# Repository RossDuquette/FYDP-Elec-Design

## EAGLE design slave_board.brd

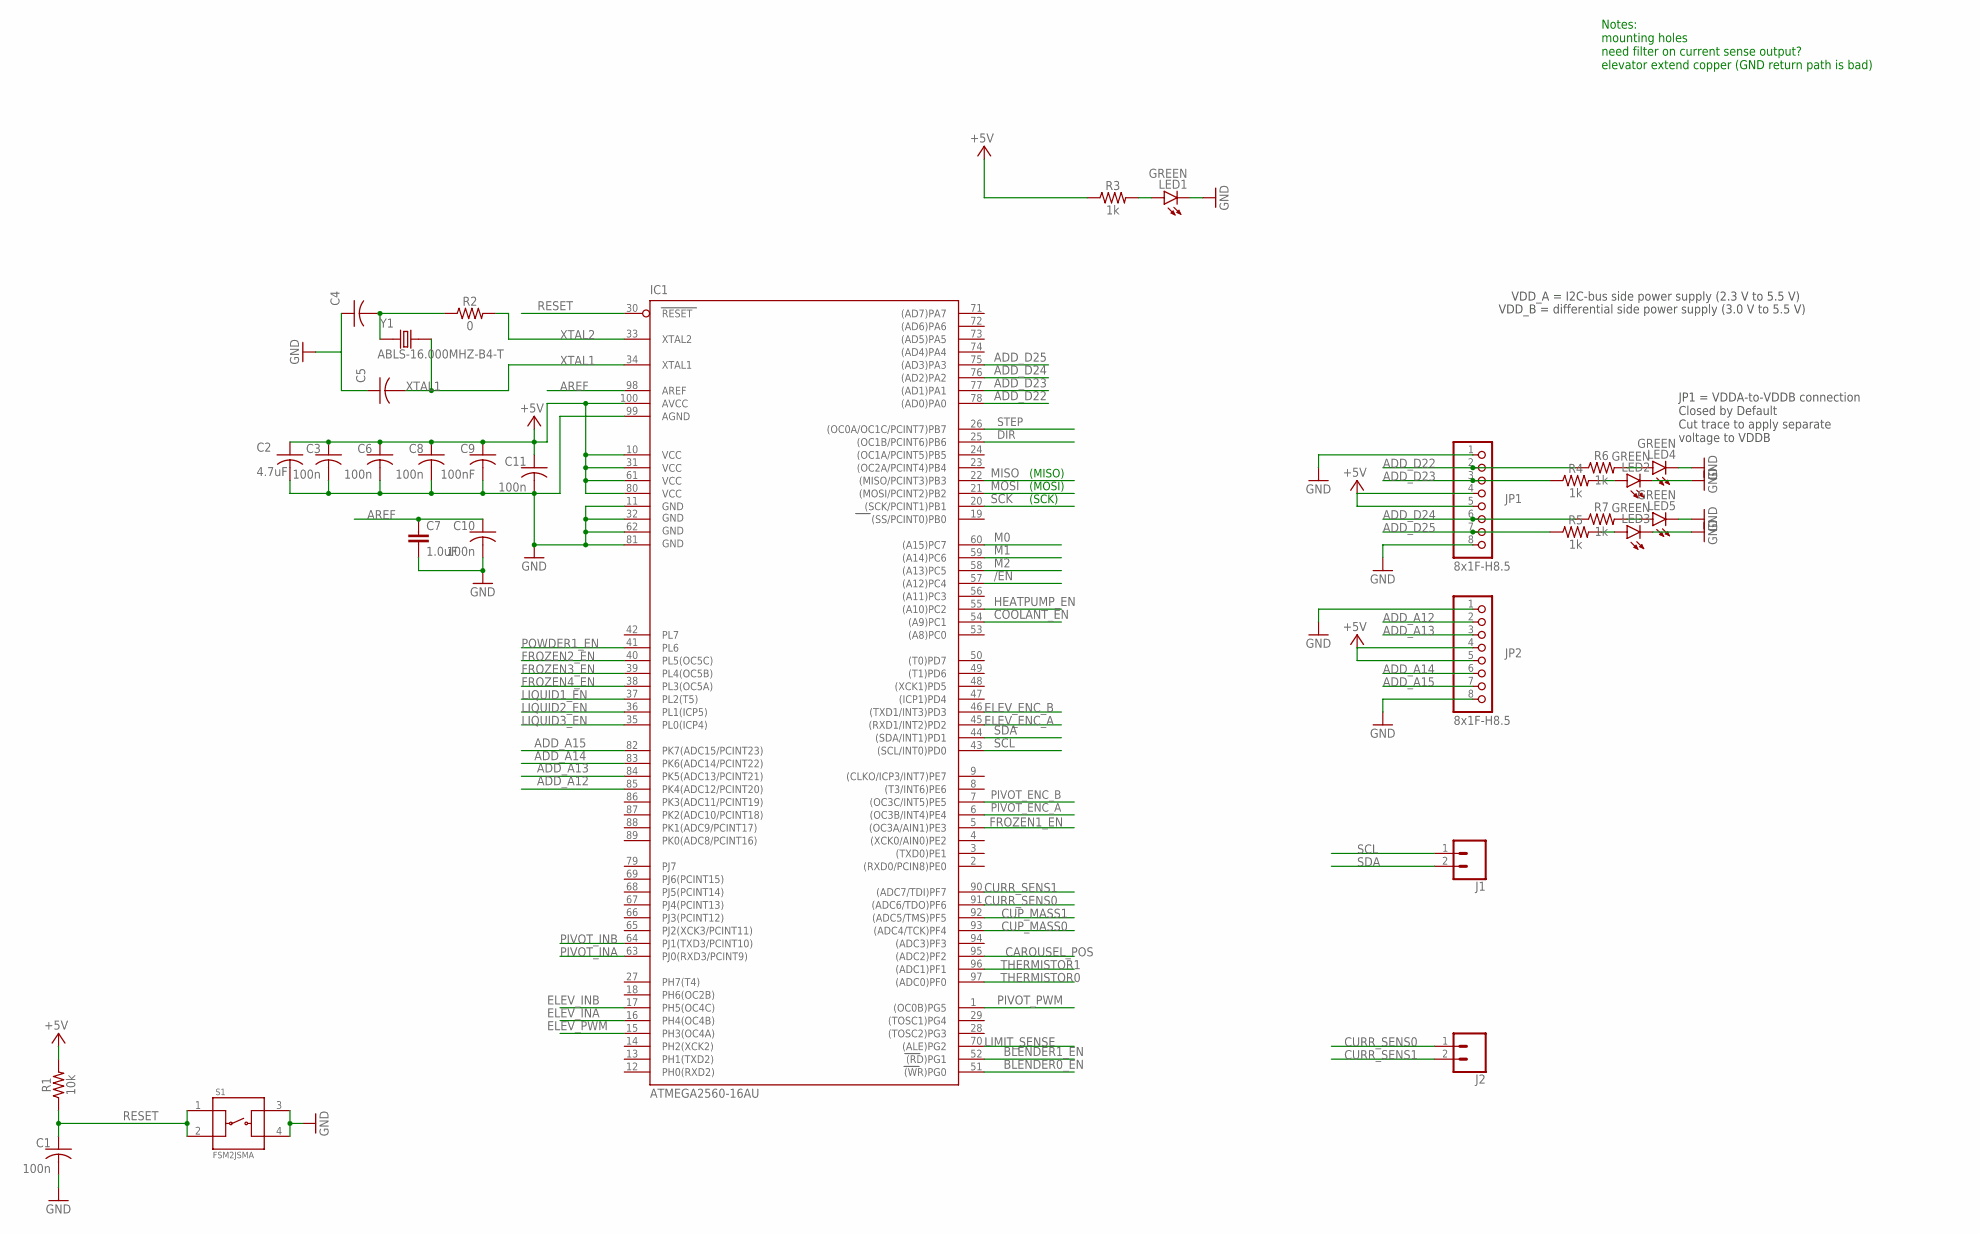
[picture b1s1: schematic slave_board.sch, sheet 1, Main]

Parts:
C1, C3, C6, C8, C10, C11: 100n; C0603
C2: 4.7uF; C0603
C4, C5: 15pF; C0603
C7: 1.0uF; 0603
C9: 100nF; C0603
IC1: ATMEGA2560-16AU; TQFP100
J1, J2: CONN_02; 1X02
JP1, JP2: 8x1F-H8.5; 1X08
LED1, LED2, LED3, LED4, LED5: GREEN; CHIP-LED0805
R1: 10k; 0603
R2: 0; 0603
R3, R4, R5, R6, R7: 1k; 0603
S1: FSM2JSMA
Y1: ABLS-16.000MHZ-B4-T

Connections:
+5V: C2.1, C3.1, C6.1, C8.1, C9.1, C11.1, IC1.10 (VCC), IC1.31 (VCC1), IC1.61 (VCC2), IC1.80 (VCC3), IC1.100 (AVCC), JP1.4, JP1.5, JP2.4, JP2.5, R1.2, R3.1; also elsewhere on the board
/EN: IC1.57 ((A12)PC4); also elsewhere on the board
ADD_A12: IC1.85 (PK4(ADC12/PCINT20)), JP2.2
ADD_A13: IC1.84 (PK5(ADC13/PCINT21)), JP2.3
ADD_A14: IC1.83 (PK6(ADC14/PCINT22)), JP2.6
ADD_A15: IC1.82 (PK7(ADC15/PCINT23)), JP2.7
ADD_D22: IC1.78 ((AD0)PA0), JP1.2, R6.1
ADD_D23: IC1.77 ((AD1)PA1), JP1.3, R4.1
ADD_D24: IC1.76 ((AD2)PA2), JP1.6, R7.1
ADD_D25: IC1.75 ((AD3)PA3), JP1.7, R5.1
AREF: C7.1, C10.1, IC1.98 (AREF)
BLENDER0_EN: IC1.51 ((WR)PG0); also elsewhere on the board
BLENDER1_EN: IC1.52 ((RD)PG1); also elsewhere on the board
CAROUSEL_POS: IC1.95 ((ADC2)PF2); also elsewhere on the board
COOLANT_EN: IC1.54 ((A9)PC1); also elsewhere on the board
CUP_MASS0: IC1.93 ((ADC4/TCK)PF4); also elsewhere on the board
CUP_MASS1: IC1.92 ((ADC5/TMS)PF5); also elsewhere on the board
CURR_SENS0: IC1.91 ((ADC6/TDO)PF6), J2.1; also elsewhere on the board
CURR_SENS1: IC1.90 ((ADC7/TDI)PF7), J2.2; also elsewhere on the board
DIR: IC1.25 ((OC1B/PCINT6)PB6); also elsewhere on the board
ELEV_ENC_A: IC1.45 ((RXD1/INT2)PD2); also elsewhere on the board
ELEV_ENC_B: IC1.46 ((TXD1/INT3)PD3); also elsewhere on the board
ELEV_INA: IC1.16 (PH4(OC4B)); also elsewhere on the board
ELEV_INB: IC1.17 (PH5(OC4C)); also elsewhere on the board
ELEV_PWM: IC1.15 (PH3(OC4A)); also elsewhere on the board
FROZEN1_EN: IC1.5 ((OC3A/AIN1)PE3); also elsewhere on the board
FROZEN2_EN: IC1.40 (PL5(OC5C)); also elsewhere on the board
FROZEN3_EN: IC1.39 (PL4(OC5B)); also elsewhere on the board
FROZEN4_EN: IC1.38 (PL3(OC5A)); also elsewhere on the board
GND: C1.2, C2.2, C3.2, C4.1, C5.1, C6.2, C7.2, C8.2, C9.2, C10.2, C11.2, IC1.11 (GND), IC1.32 (GND1), IC1.62 (GND2), IC1.81 (GND3), IC1.99 (AGND), JP1.1, JP1.8, JP2.1, JP2.8, LED1.C, LED2.C, LED3.C, LED4.C, LED5.C, S1.3, S1.4; also elsewhere on the board
HEATPUMP_EN: IC1.55 ((A10)PC2); also elsewhere on the board
LIMIT_SENSE: IC1.70 ((ALE)PG2); also elsewhere on the board
LIQUID1_EN: IC1.37 (PL2(T5)); also elsewhere on the board
LIQUID2_EN: IC1.36 (PL1(ICP5)); also elsewhere on the board
LIQUID3_EN: IC1.35 (PL0(ICP4)); also elsewhere on the board
M0: IC1.60 ((A15)PC7); also elsewhere on the board
M1: IC1.59 ((A14)PC6); also elsewhere on the board
M2: IC1.58 ((A13)PC5); also elsewhere on the board
MISO: IC1.22 ((MISO/PCINT3)PB3); also elsewhere on the board
MOSI: IC1.21 ((MOSI/PCINT2)PB2); also elsewhere on the board
unnamed: LED5.A, R7.2
unnamed: LED1.A, R3.2
unnamed: LED3.A, R5.2
unnamed: LED4.A, R6.2
unnamed: LED2.A, R4.2
unnamed: C4.2, R2.1, Y1.1
PIVOT_ENC_A: IC1.6 ((OC3B/INT4)PE4); also elsewhere on the board
PIVOT_ENC_B: IC1.7 ((OC3C/INT5)PE5); also elsewhere on the board
PIVOT_INA: IC1.63 (PJ0(RXD3/PCINT9)); also elsewhere on the board
PIVOT_INB: IC1.64 (PJ1(TXD3/PCINT10)); also elsewhere on the board
PIVOT_PWM: IC1.1 ((OC0B)PG5); also elsewhere on the board
POWDER1_EN: IC1.41 (PL6); also elsewhere on the board
RESET: C1.1, IC1.30 (RESET), R1.1, S1.1, S1.2; also elsewhere on the board
SCK: IC1.20 ((SCK/PCINT1)PB1); also elsewhere on the board
SCL: IC1.43 ((SCL/INT0)PD0), J1.1; also elsewhere on the board
SDA: IC1.44 ((SDA/INT1)PD1), J1.2; also elsewhere on the board
STEP: IC1.26 ((OC0A/OC1C/PCINT7)PB7); also elsewhere on the board
THERMISTOR0: IC1.97 ((ADC0)PF0); also elsewhere on the board
THERMISTOR1: IC1.96 ((ADC1)PF1); also elsewhere on the board
XTAL1: C5.2, IC1.34 (XTAL1), Y1.2
XTAL2: IC1.33 (XTAL2), R2.2

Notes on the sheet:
Notes: mounting holes need filter on current sense output? elevator extend copper (GND return path is bad)
JP1 = VDDA-to-VDDB connection Closed by Default Cut trace to apply separate voltage to VDDB
VDD_A = I2C-bus side power supply (2.3 V to 5.5 V)
VDD_B = differential side power supply (3.0 V to 5.5 V)
(MISO)
(SCK)
(MOSI)

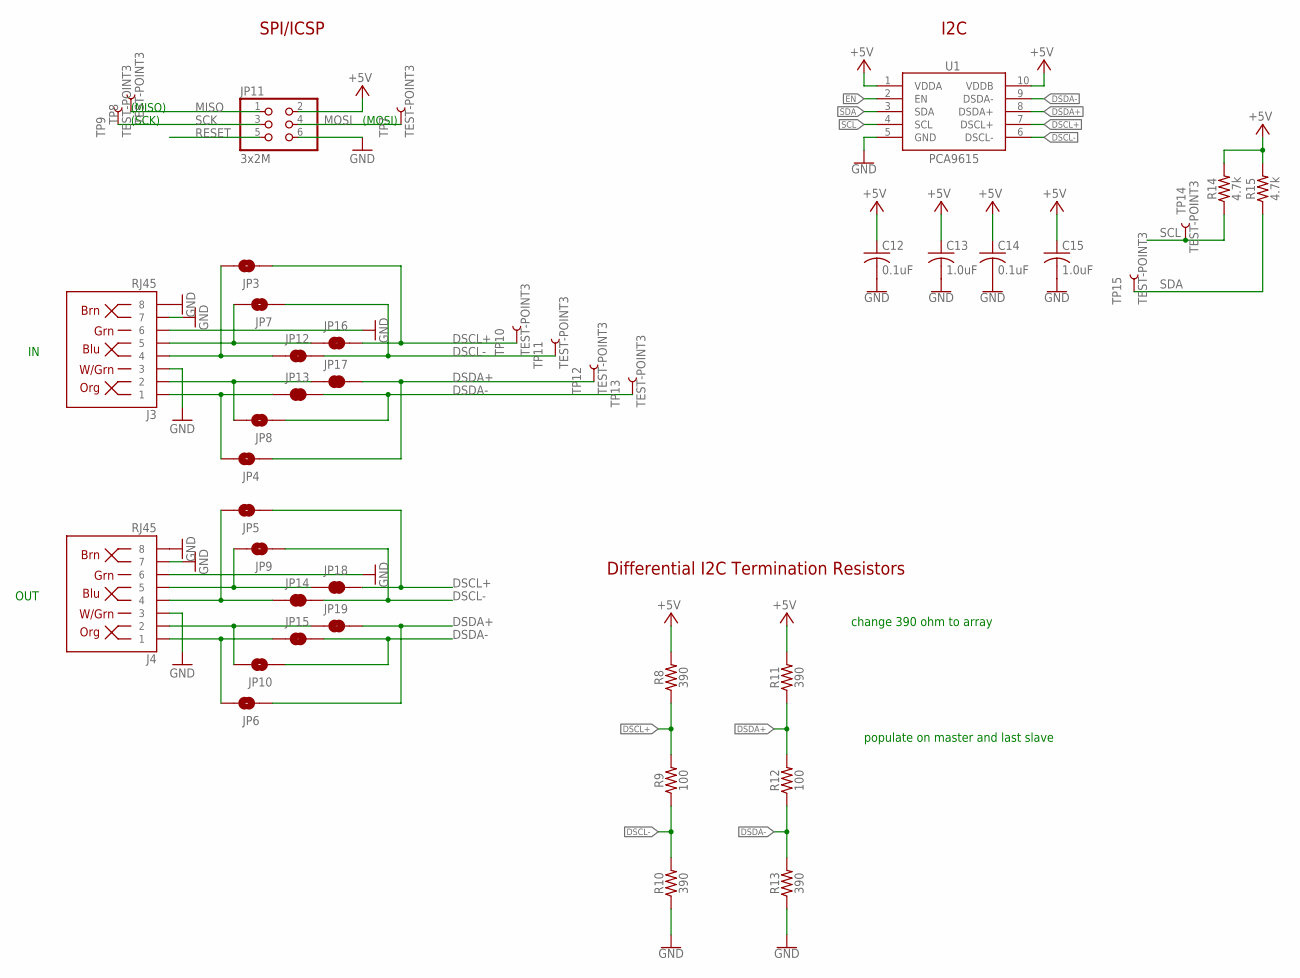
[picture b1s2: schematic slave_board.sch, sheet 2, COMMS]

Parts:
C12, C14: 0.1uF; C0603
C13, C15: 1.0uF; C0603
J3, J4: RJ45; RJ45-8
JP3, JP4, JP5, JP6, JP7, JP8, JP9, JP10: JUMPER-SMT_2_NO_NO-SILK; SMT-JUMPER_2_NO_NO-SILK
JP11: 3x2M; 2X03
JP12, JP13, JP14, JP15, JP16, JP17, JP18, JP19: JUMPER-SMT_2_NC_TRACE_NO-SILK; SMT-JUMPER_2_NC_TRACE_NO-SILK
R8, R10, R11, R13: 390; 0603
R9, R12: 100; 0603
R14, R15: 4.7k; 0603
TP7, TP8, TP9, TP10, TP11, TP12, TP13, TP14, TP15: TEST-POINT3; PAD.03X.03
U1: PCA9615; SPARKFUN-IC-COMMS_TSSOP10

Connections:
+5V: C12.1, C13.1, C14.1, C15.1, JP11.2, R8.2, R11.2, R14.2, R15.2, U1.1 (VDDA), U1.10 (VDDB); also elsewhere on the board
DSCL+: J3.5, J4.5, JP3.1, JP5.1, JP7.2, JP9.2, JP16.1, JP16.2, JP18.1, JP18.2, R8.1, R9.2, TP10.P$1, U1.7 (DSCL+)
DSCL-: J3.4, J4.4, JP3.2, JP5.2, JP7.1, JP9.1, JP12.1, JP12.2, JP14.1, JP14.2, R9.1, R10.2, TP11.P$1, U1.6 (DSCL-)
DSDA+: J3.2, J4.2, JP4.1, JP6.1, JP8.2, JP10.2, JP17.1, JP17.2, JP19.1, JP19.2, R11.1, R12.2, TP12.P$1, U1.8 (DSDA+)
DSDA-: J3.1, J4.1, JP4.2, JP6.2, JP8.1, JP10.1, JP13.1, JP13.2, JP15.1, JP15.2, R12.1, R13.2, TP13.P$1, U1.9 (DSDA-)
EN: U1.2 (EN)
GND: C12.2, C13.2, C14.2, C15.2, J3.3, J3.6, J3.7, J3.8, J4.3, J4.6, J4.7, J4.8, JP11.6, R10.1, R13.1, U1.5 (GND); also elsewhere on the board
MISO: JP11.1, TP8.P$1; also elsewhere on the board
MOSI: JP11.4, TP7.P$1; also elsewhere on the board
RESET: JP11.5; also elsewhere on the board
SCK: JP11.3, TP9.P$1; also elsewhere on the board
SCL: R14.1, TP14.P$1, U1.4 (SCL); also elsewhere on the board
SDA: R15.1, TP15.P$1, U1.3 (SDA); also elsewhere on the board

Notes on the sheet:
(SCK)
(MISO)
(MOSI)
I2C
SPI/ICSP
Differential I2C Termination Resistors
OUT
populate on master and last slave
change 390 ohm to array

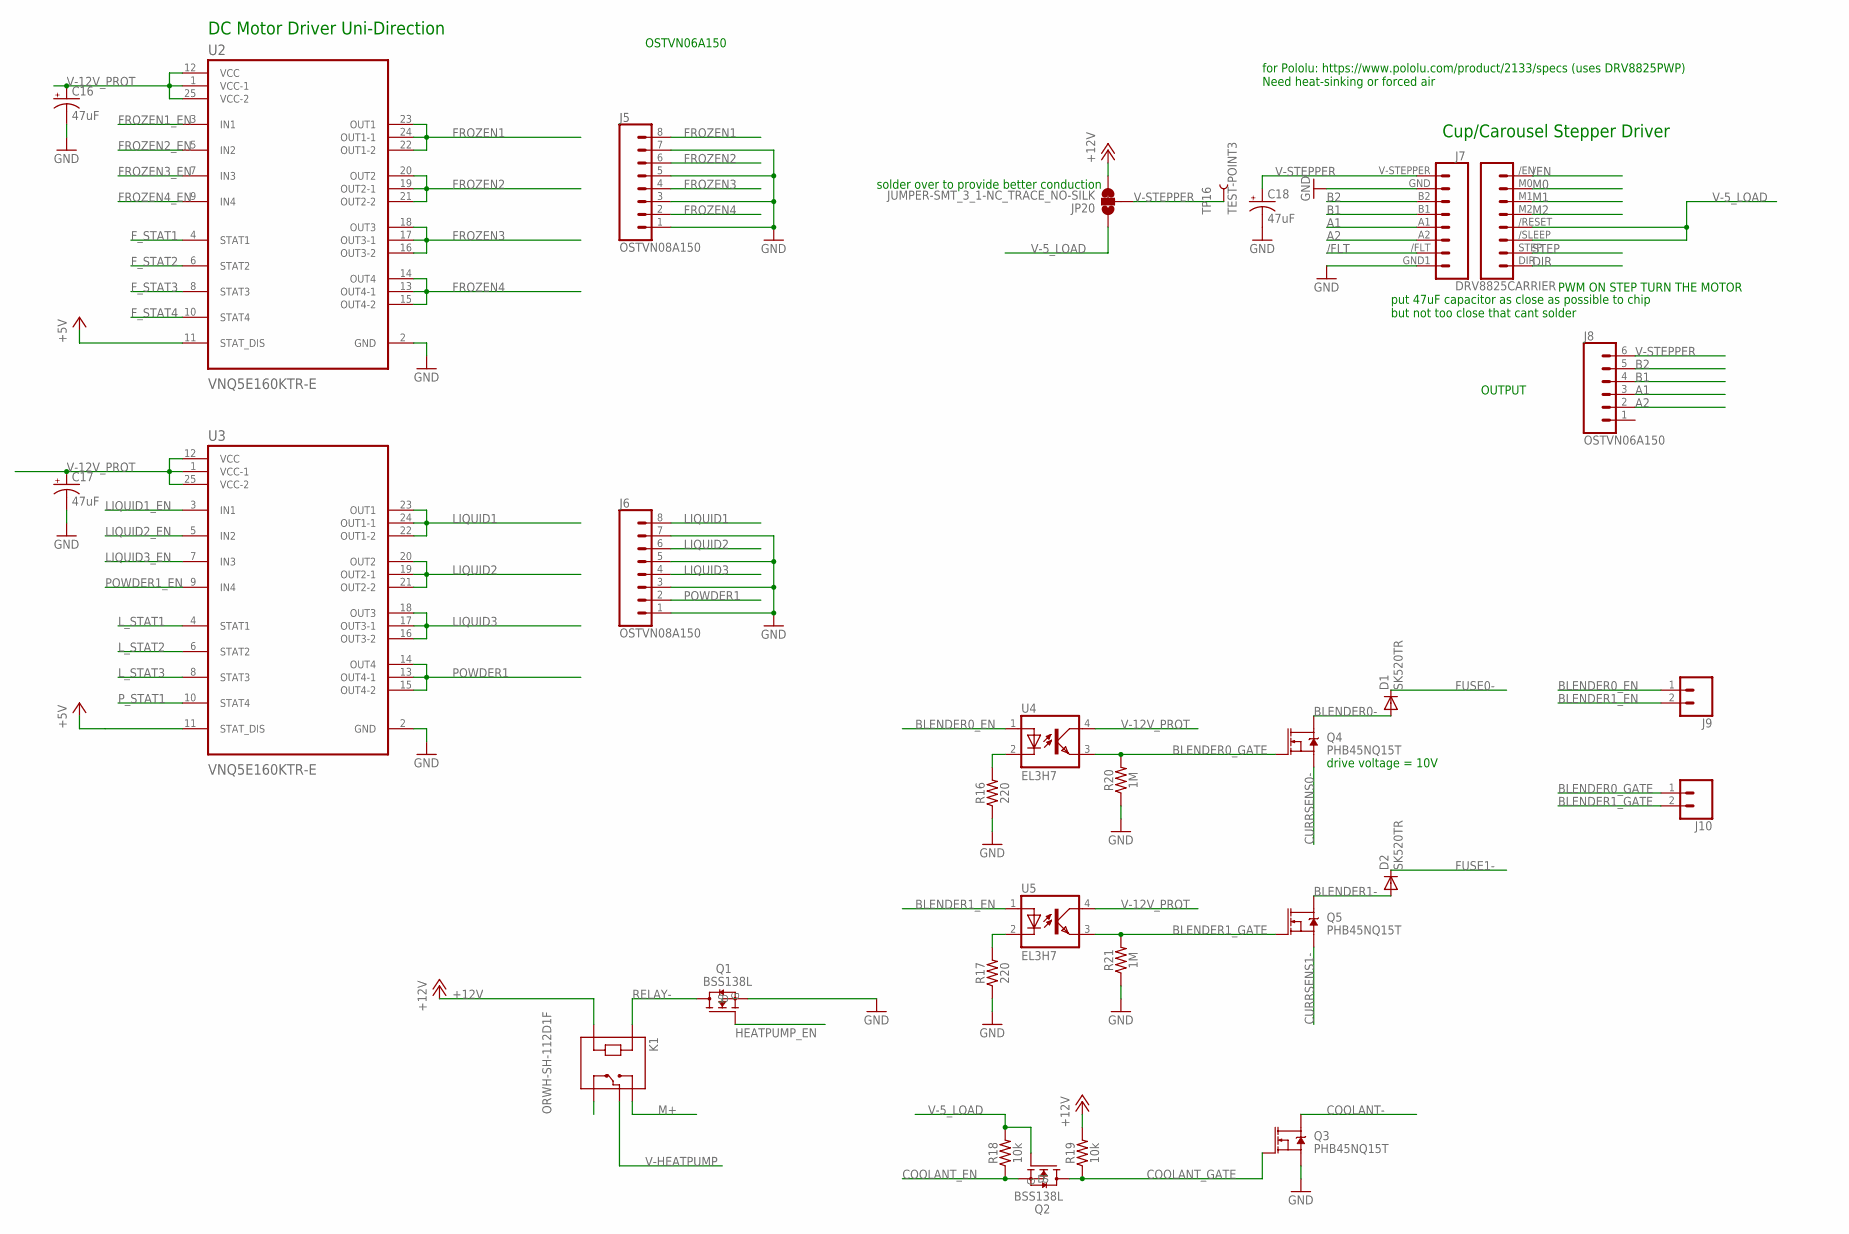
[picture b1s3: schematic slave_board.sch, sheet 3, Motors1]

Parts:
C16, C17, C18: 47uF; PANASONIC_D
D1, D2: SK520TR
J5, J6: OSTVN08A150; 8PIN_SCREW_TERMINAL
J7: DRV8825CARRIER
J8: OSTVN06A150; 6PIN_SCREW_TERMINAL
J9, J10: CONN_02; 1X02
JP20: JUMPER-SMT_3_1-NC_TRACE_NO-SILK; SMT-JUMPER_3_1-NC_TRACE_NO-SILK
K1: ORWH-SH-112D1F
Q1, Q2: BSS138L
Q3, Q4, Q5: PHB45NQ15T
R16, R17: 220; 0603
R18, R19: 10k; 0603
R20, R21: 1M; 0603
TP16: TEST-POINT3; PAD.03X.03
U2, U3: VNQ5E160KTR-E; SOP80P1030X245-25N
U4, U5: EL3H7

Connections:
+5V: U2.11 (STAT_DIS), U3.11 (STAT_DIS); also elsewhere on the board
+12V: JP20.3, K1.A2, R19.2; also elsewhere on the board
/EN: J7./EN (16); also elsewhere on the board
/FLT: J7./FLT (7)
A1: J7.A1 (5), J8.3
A2: J7.A2 (6), J8.2
B1: J7.B1 (4), J8.4
B2: J7.B2 (3), J8.5
BLENDER0-: D1.1 (A), Q4.2 (D); also elsewhere on the board
BLENDER0_EN: J9.1, U4.1; also elsewhere on the board
BLENDER0_GATE: J10.1, Q4.1 (G), R20.2, U4.3
BLENDER1-: D2.1 (A), Q5.2 (D); also elsewhere on the board
BLENDER1_EN: J9.2, U5.1; also elsewhere on the board
BLENDER1_GATE: J10.2, Q5.1 (G), R21.2, U5.3
COOLANT-: Q3.2 (D); also elsewhere on the board
COOLANT_EN: Q2.S, R18.1; also elsewhere on the board
COOLANT_GATE: Q2.D, Q3.1 (G), R19.1
CURRSENS0-: Q4.3 (S); also elsewhere on the board
CURRSENS1-: Q5.3 (S); also elsewhere on the board
DIR: J7.DIR (9); also elsewhere on the board
FROZEN1: J5.8, U2.22 (OUT1-2), U2.23 (OUT1), U2.24 (OUT1-1)
FROZEN1_EN: U2.3 (IN1); also elsewhere on the board
FROZEN2: J5.6, U2.19 (OUT2-1), U2.20 (OUT2), U2.21 (OUT2-2)
FROZEN2_EN: U2.5 (IN2); also elsewhere on the board
FROZEN3: J5.4, U2.16 (OUT3-2), U2.17 (OUT3-1), U2.18 (OUT3)
FROZEN3_EN: U2.7 (IN3); also elsewhere on the board
FROZEN4: J5.2, U2.13 (OUT4-1), U2.14 (OUT4), U2.15 (OUT4-2)
FROZEN4_EN: U2.9 (IN4); also elsewhere on the board
FUSE0-: D1.2 (C); also elsewhere on the board
FUSE1-: D2.2 (C); also elsewhere on the board
F_STAT1: U2.4 (STAT1)
F_STAT2: U2.6 (STAT2)
F_STAT3: U2.8 (STAT3)
F_STAT4: U2.10 (STAT4)
GND: C16.-, C17.-, C18.-, J5.1, J5.3, J5.5, J5.7, J6.1, J6.3, J6.5, J6.7, J7.GND (2), J7.GND1 (8), Q1.S, Q3.3 (S), R16.1, R17.1, R20.1, R21.1, U2.2 (GND), U3.2 (GND); also elsewhere on the board
HEATPUMP_EN: Q1.G; also elsewhere on the board
LIQUID1: J6.8, U3.22 (OUT1-2), U3.23 (OUT1), U3.24 (OUT1-1)
LIQUID1_EN: U3.3 (IN1); also elsewhere on the board
LIQUID2: J6.6, U3.19 (OUT2-1), U3.20 (OUT2), U3.21 (OUT2-2)
LIQUID2_EN: U3.5 (IN2); also elsewhere on the board
LIQUID3: J6.4, U3.16 (OUT3-2), U3.17 (OUT3-1), U3.18 (OUT3)
LIQUID3_EN: U3.7 (IN3); also elsewhere on the board
L_STAT1: U3.4 (STAT1)
L_STAT2: U3.6 (STAT2)
L_STAT3: U3.8 (STAT3)
M0: J7.M0 (15); also elsewhere on the board
M1: J7.M1 (14); also elsewhere on the board
M2: J7.M2 (13); also elsewhere on the board
M+: K1.NO; also elsewhere on the board
unnamed: R17.2, U5.2
unnamed: R16.2, U4.2
POWDER1: J6.2, U3.13 (OUT4-1), U3.14 (OUT4), U3.15 (OUT4-2)
POWDER1_EN: U3.9 (IN4); also elsewhere on the board
P_STAT1: U3.10 (STAT4)
RELAY-: K1.A1, Q1.D
STEP: J7.STEP (10); also elsewhere on the board
V-5_LOAD: J7./RESET (12), J7./SLEEP (11), JP20.1, Q2.G, R18.2; also elsewhere on the board
V-12V_PROT: C16.+, C17.+, U2.1 (VCC-1), U2.12 (VCC), U2.25 (VCC-2), U3.1 (VCC-1), U3.12 (VCC), U3.25 (VCC-2), U4.4, U5.4; also elsewhere on the board
V-HEATPUMP: K1.COM; also elsewhere on the board
V-STEPPER: C18.+, J7.V-STEPPER (1), J8.6, JP20.2, TP16.P$1

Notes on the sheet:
DC Motor Driver Uni-Direction
Cup/Carousel Stepper Driver
for Pololu: https://www.pololu.com/product/2133/specs (uses DRV8825PWP) Need heat-sinking or forced air
put 47uF capacitor as close as possible to chip but not too close that cant solder
OUTPUT
PWM ON STEP TURN THE MOTOR
solder over to provide better conduction
drive voltage = 10V
OSTVN06A150

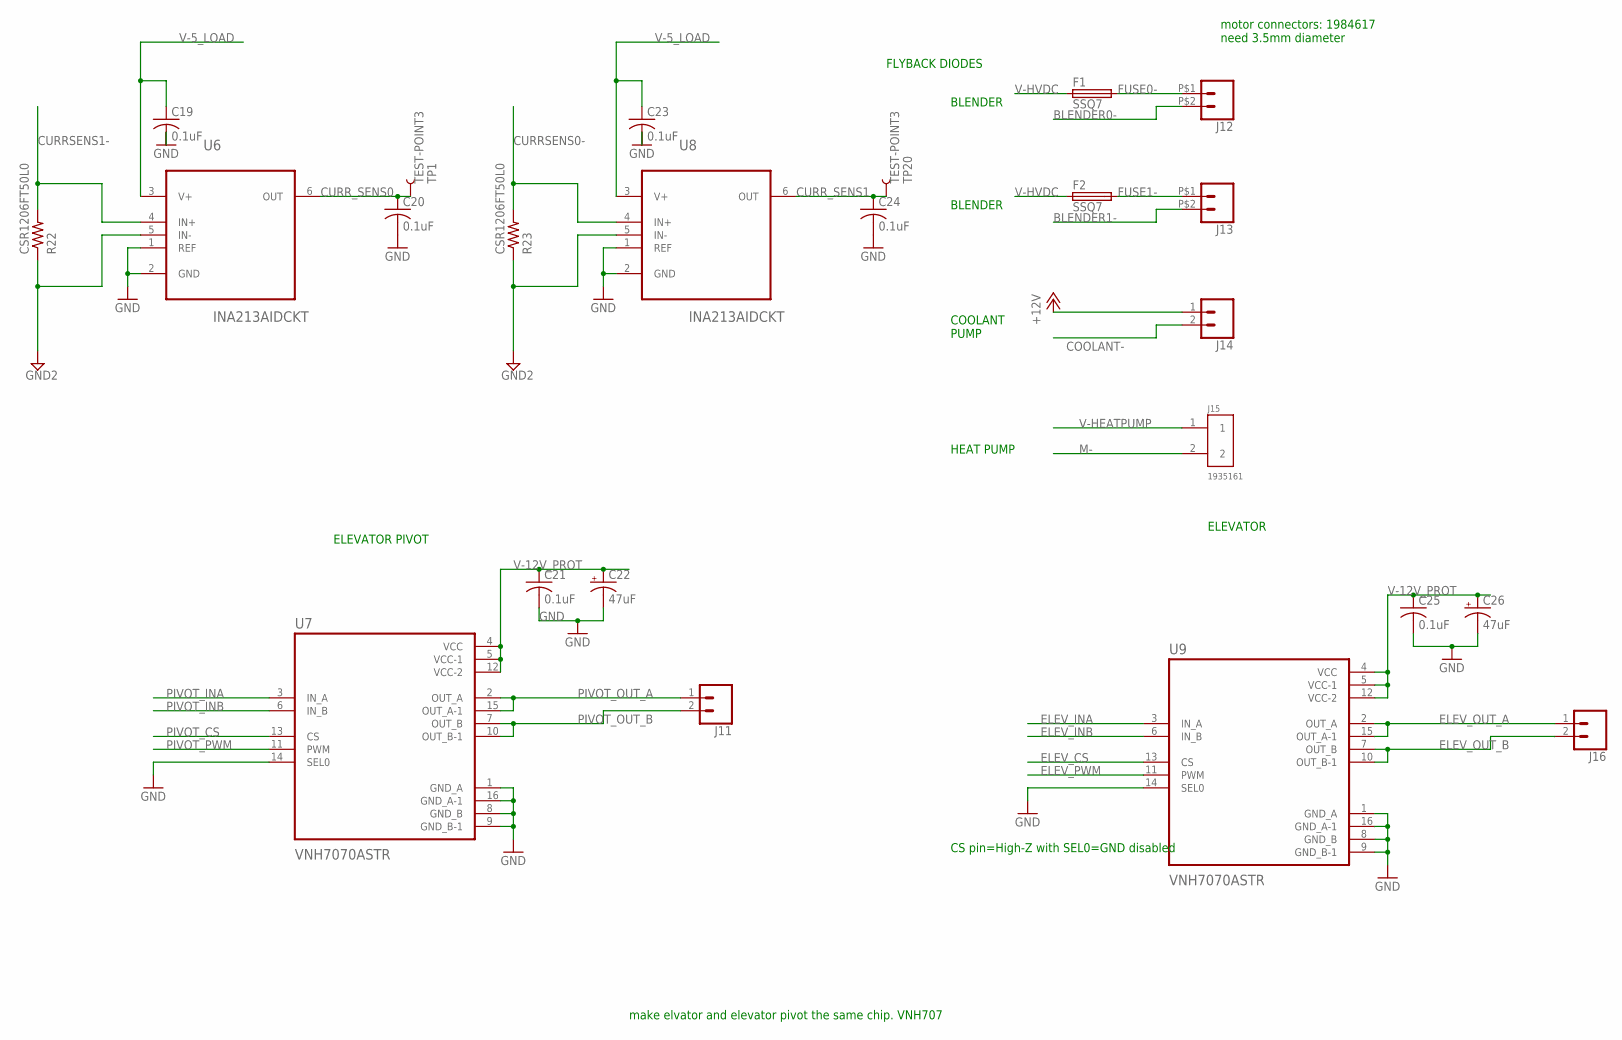
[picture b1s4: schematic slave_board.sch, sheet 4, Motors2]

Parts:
C19, C20, C21, C23, C24, C25: 0.1uF; C0603
C22, C26: 47uF; PANASONIC_D
F1, F2: SSQ7
J11, J14, J16: CONN_02; 1X02
J12, J13: CONN_02PTH2; 1X02_BIG
J15: 1935161; PHOENIX_1935161
R22, R23: CSR1206FT50L0
TP1, TP20: TEST-POINT3; PAD.03X.03
U6, U8: INA213AIDCKT; SOT65P210X110-6N
U7, U9: VNH7070ASTR

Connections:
+12V: J14.1; also elsewhere on the board
BLENDER0-: J12.P$2 (2); also elsewhere on the board
BLENDER1-: J13.P$2 (2); also elsewhere on the board
COOLANT-: J14.2; also elsewhere on the board
CURRSENS0-: R23.2, U8.4 (IN+); also elsewhere on the board
CURRSENS1-: R22.2, U6.4 (IN+); also elsewhere on the board
CURR_SENS0: C20.1, TP1.P$1, U6.6 (OUT); also elsewhere on the board
CURR_SENS1: C24.1, TP20.P$1, U8.6 (OUT); also elsewhere on the board
ELEV_CS: U9.13 (CS)
ELEV_INA: U9.3 (IN_A); also elsewhere on the board
ELEV_INB: U9.6 (IN_B); also elsewhere on the board
ELEV_OUT_A: J16.1, U9.2 (OUT_A), U9.15 (OUT_A-1)
ELEV_OUT_B: J16.2, U9.7 (OUT_B), U9.10 (OUT_B-1)
ELEV_PWM: U9.11 (PWM); also elsewhere on the board
FUSE0-: F1.2, J12.P$1 (1); also elsewhere on the board
FUSE1-: F2.2, J13.P$1 (1); also elsewhere on the board
GND: C19.2, C20.2, C21.2, C22.-, C23.2, C24.2, C25.2, C26.-, U6.1 (REF), U6.2 (GND), U7.1 (GND_A), U7.8 (GND_B), U7.9 (GND_B-1), U7.14 (SEL0), U7.16 (GND_A-1), U8.1 (REF), U8.2 (GND), U9.1 (GND_A), U9.8 (GND_B), U9.9 (GND_B-1), U9.14 (SEL0), U9.16 (GND_A-1); also elsewhere on the board
GND2: R22.1, R23.1, U6.5 (IN-), U8.5 (IN-); also elsewhere on the board
M-: J15.2; also elsewhere on the board
PIVOT_CS: U7.13 (CS)
PIVOT_INA: U7.3 (IN_A); also elsewhere on the board
PIVOT_INB: U7.6 (IN_B); also elsewhere on the board
PIVOT_OUT_A: J11.1, U7.2 (OUT_A), U7.15 (OUT_A-1)
PIVOT_OUT_B: J11.2, U7.7 (OUT_B), U7.10 (OUT_B-1)
PIVOT_PWM: U7.11 (PWM); also elsewhere on the board
V-5_LOAD: C19.1, C23.1, U6.3 (V+), U8.3 (V+); also elsewhere on the board
V-12V_PROT: C21.1, C22.+, C25.1, C26.+, U7.4 (VCC), U7.5 (VCC-1), U7.12 (VCC-2), U9.4 (VCC), U9.5 (VCC-1), U9.12 (VCC-2); also elsewhere on the board
V-HEATPUMP: J15.1; also elsewhere on the board
V-HVDC: F1.1, F2.1; also elsewhere on the board

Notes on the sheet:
ELEVATOR PIVOT
ELEVATOR
CS pin=High-Z with SEL0=GND disabled
make elvator and elevator pivot the same chip. VNH707
FLYBACK DIODES
BLENDER
HEAT PUMP
COOLANT PUMP
motor connectors: 1984617 need 3.5mm diameter

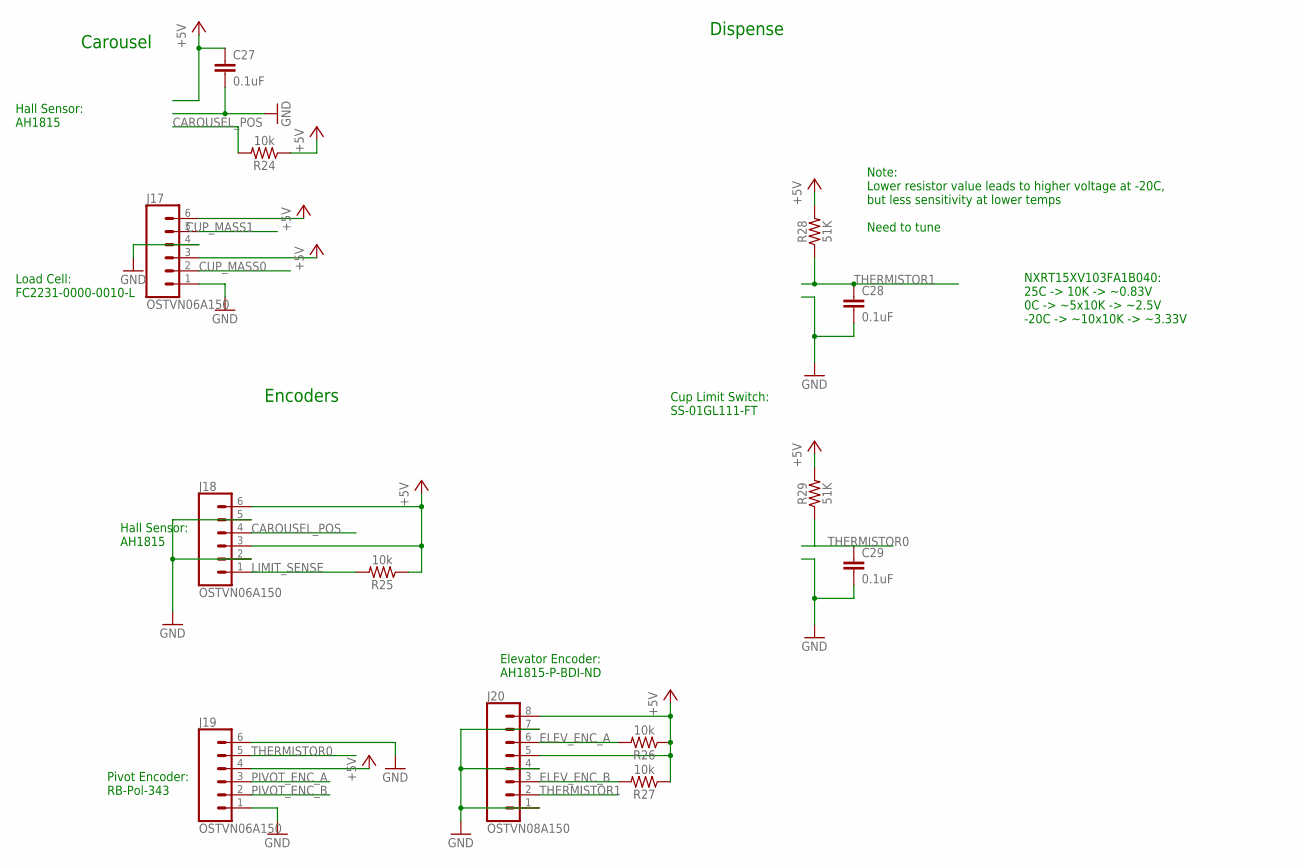
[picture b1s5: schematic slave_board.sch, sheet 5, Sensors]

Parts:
C27, C28, C29: 0.1uF; 0603
J17, J18, J19: OSTVN06A150; 6PIN_SCREW_TERMINAL
J20: OSTVN08A150; 8PIN_SCREW_TERMINAL
R24, R25, R26, R27: 10k; 0603
R28, R29: 51K; 0603

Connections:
+5V: C27.1, J17.3, J17.6, J18.3, J18.6, J19.4, J20.5, J20.8, R24.1, R25.1, R26.1, R27.1, R28.2, R29.2; also elsewhere on the board
CAROUSEL_POS: J18.4, R24.2; also elsewhere on the board
CUP_MASS0: J17.2; also elsewhere on the board
CUP_MASS1: J17.5; also elsewhere on the board
ELEV_ENC_A: J20.6, R26.2; also elsewhere on the board
ELEV_ENC_B: J20.3, R27.2; also elsewhere on the board
GND: C27.2, C28.2, C29.2, J17.1, J17.4, J18.2, J18.5, J19.1, J19.6, J20.1, J20.4, J20.7; also elsewhere on the board
LIMIT_SENSE: J18.1, R25.2; also elsewhere on the board
PIVOT_ENC_A: J19.3; also elsewhere on the board
PIVOT_ENC_B: J19.2; also elsewhere on the board
THERMISTOR0: C29.1, J19.5, R29.1; also elsewhere on the board
THERMISTOR1: C28.1, J20.2, R28.1; also elsewhere on the board

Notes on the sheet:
Carousel
Dispense
Hall Sensor: AH1815
Load Cell: FC2231-0000-0010-L
Cup Limit Switch: SS-01GL111-FT
NXRT15XV103FA1B040: 25C -> 10K -> ~0.83V 0C -> ~5x10K -> ~2.5V -20C -> ~10x10K -> ~3.33V
Note: Lower resistor value leads to higher voltage at -20C, but less sensitivity at lower temps Need to tune
Encoders
Pivot Encoder: RB-Pol-343
Elevator Encoder: AH1815-P-BDI-ND

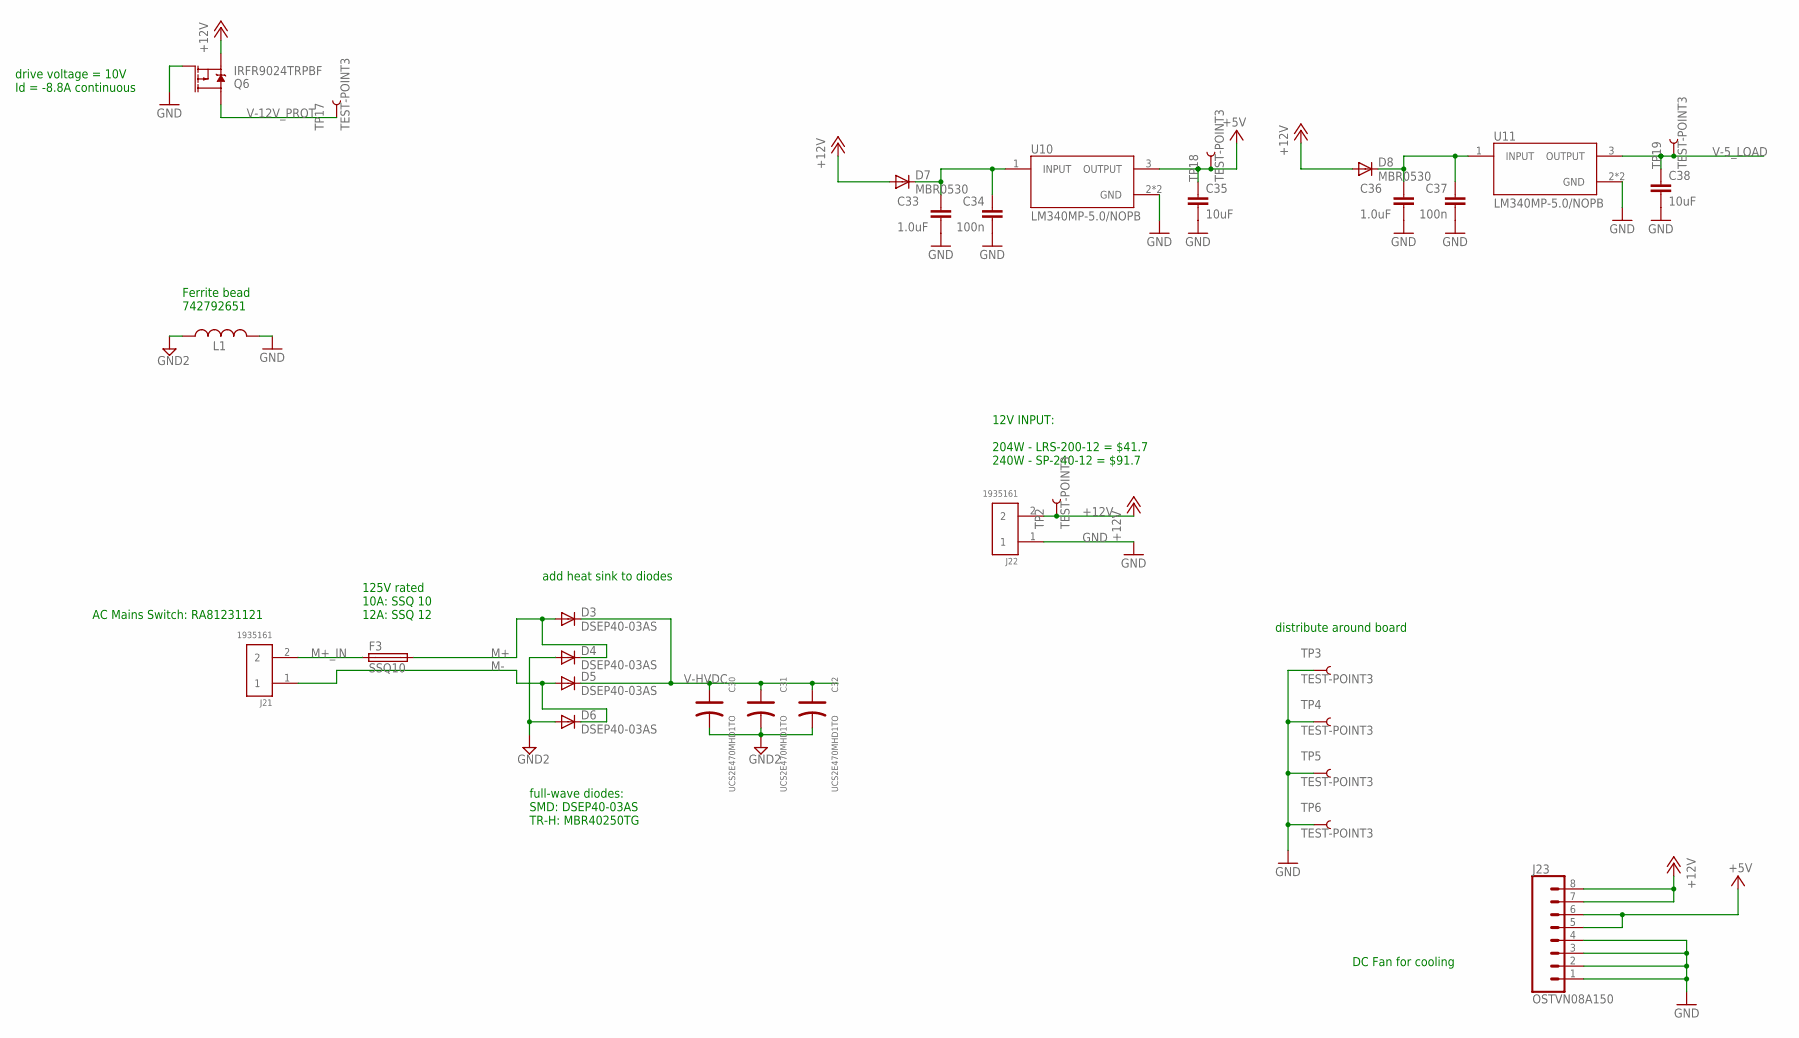
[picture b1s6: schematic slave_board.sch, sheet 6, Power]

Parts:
C30, C31, C32: UCS2E470MHD1TO
C33, C36: 1.0uF; 0603
C34, C37: 100n; C0603-ROUND
C35, C38: 10uF; 0805
D3, D4, D5, D6: DSEP40-03AS
D7, D8: MBR0530
F3: SSQ10
J21, J22: 1935161; PHOENIX_1935161
J23: OSTVN08A150; 8PIN_SCREW_TERMINAL
L1: 742792651
Q6: IRFR9024TRPBF
TP2, TP3, TP4, TP5, TP6, TP17, TP18, TP19: TEST-POINT3; PAD.03X.03
U10, U11: LM340MP-5.0/NOPB; SOT230P700X180-4N

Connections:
+5V: C35.1, J23.5, J23.6, TP18.P$1, U10.3 (OUTPUT); also elsewhere on the board
+12V: D7.1 (A), D8.1 (A), J22.2, J23.7, J23.8, Q6.S, TP2.P$1; also elsewhere on the board
GND: C33.2, C34.2, C35.2, C36.2, C37.2, C38.2, J22.1, J23.1, J23.2, J23.3, J23.4, L1.P$2 (2), Q6.G, TP3.P$1, TP4.P$1, TP5.P$1, TP6.P$1, U10.2 (GND), U10.4 (GND), U11.2 (GND), U11.4 (GND); also elsewhere on the board
GND2: C30.-, C31.-, C32.-, D4.1 (A), D4.3 (A), D6.1 (A), D6.3 (A), L1.P$1 (1); also elsewhere on the board
M+: D3.1 (A), D3.3 (A), D4.4 (C), F3.2; also elsewhere on the board
M+_IN: F3.1, J21.2
M-: D5.1 (A), D5.3 (A), D6.4 (C), J21.1; also elsewhere on the board
unnamed: C33.1, C34.1, D7.2 (C), U10.1 (INPUT)
unnamed: C36.1, C37.1, D8.2 (C), U11.1 (INPUT)
V-5_LOAD: C38.1, TP19.P$1, U11.3 (OUTPUT); also elsewhere on the board
V-12V_PROT: Q6.D, TP17.P$1; also elsewhere on the board
V-HVDC: C30.+, C31.+, C32.+, D3.4 (C), D5.4 (C); also elsewhere on the board

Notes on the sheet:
full-wave diodes: SMD: DSEP40-03AS TR-H: MBR40250TG
125V rated 10A: SSQ 10 12A: SSQ 12
12V INPUT: 204W - LRS-200-12 = $41.7 240W - SP-240-12 = $91.7
add heat sink to diodes
AC Mains Switch: RA81231121
DC Fan for cooling
drive voltage = 10V Id = -8.8A continuous
distribute around board
Ferrite bead 742792651

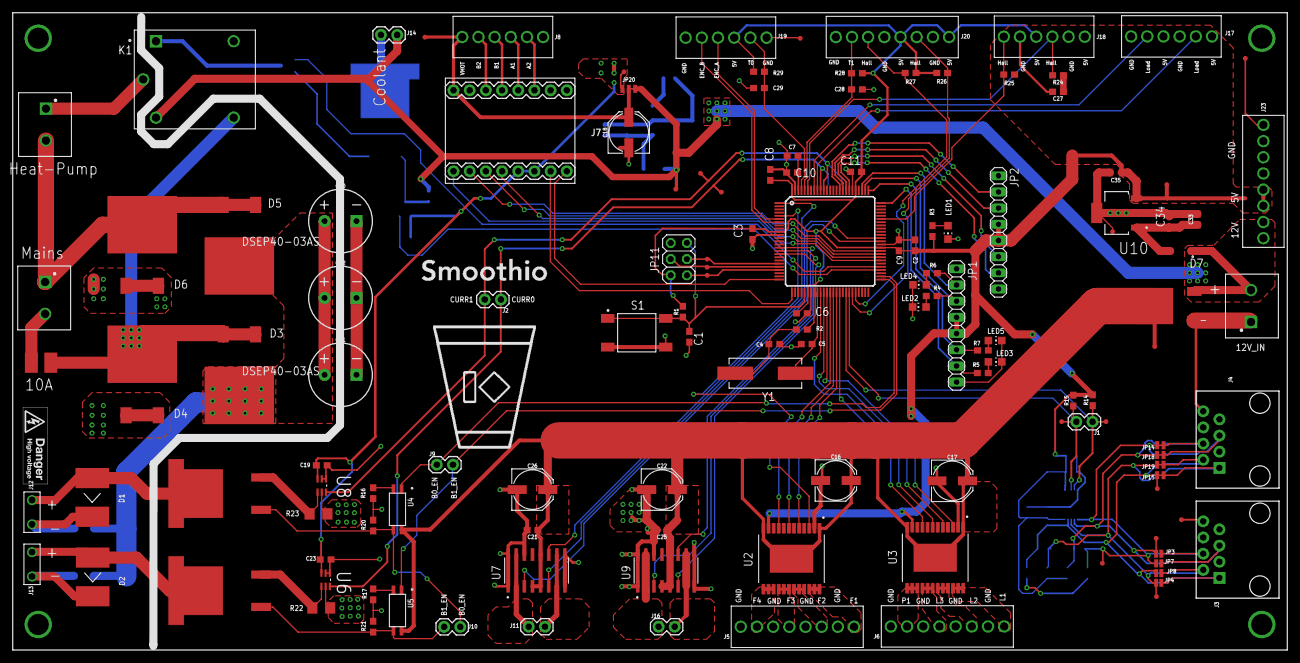
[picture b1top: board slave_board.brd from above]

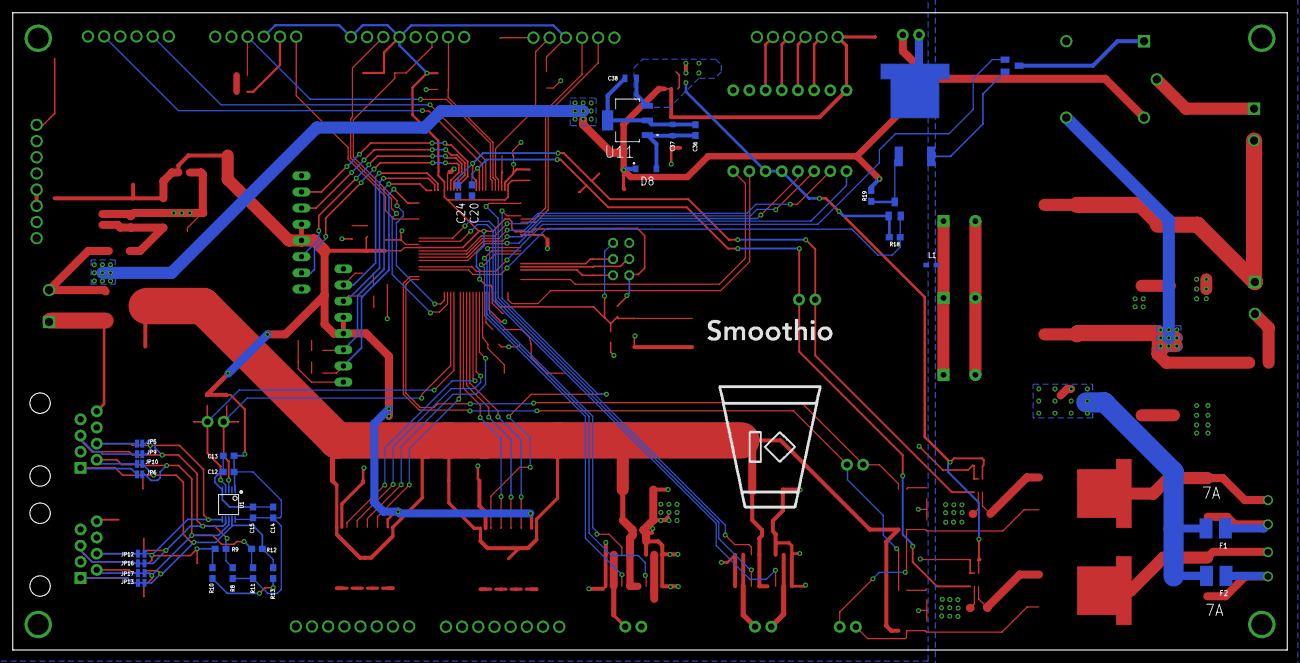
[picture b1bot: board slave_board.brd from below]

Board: 2 copper layers, 200.0 x 100.0 mm, 168 parts (34 on the bottom side), 106 nets.

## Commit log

2018-12-27 beginning of project
2018-12-27 library files
2018-12-27 more work
2018-12-27 removed some unnecessary files
2018-12-28 selected motor and full-bridge parts - see comments in sheet
2018-12-28 added some part selection - see comments in sheet
2018-12-29 added some part selection
2018-12-30 added some parts
2018-12-30 Added diode
2018-12-30 Setup
2018-12-30 Created new smoothio library
2018-12-30 full wave recitifer
2018-12-30 progress
2019-01-01 fixed ref des'
2019-01-01 added elevator motors to schem
2019-01-02 added some comments for review
2019-01-03 schematic review changes
2019-01-05 mains connector change
2019-01-05 progress on component placement
2019-01-07 rough part placement
2019-01-07 board adjustments
2019-01-08 fixed current sense
2019-01-08 turned motor driver into new part
2019-01-09 Reviewed with Danyon
2019-01-09 Added encoders
2019-01-09 Wired microcontroller
2019-01-09 merged changes and layout progress
2019-01-09 Changed net names to align with names used for mcu
2019-01-10 board progress - motors,i2c
2019-01-10 board progress - motor routing
2019-01-10 board progress - generic connections
2019-01-10 board progress - new 5V, route comms
2019-01-10 board progress - routing + new dispenser pin assignments
2019-01-10 board progress - routing + ADC pin assignment
2019-01-10 Routed mcu, except for additional pins
2019-01-10 Removed backup files
2019-01-11 board progress - routing
2019-01-11 board progress - power routing
2019-01-11 board progress - routing additional digital plus analog
2019-01-11 board progress
2019-01-13 Fixed some errors
2019-01-15 Resize board, add mounting holes
2019-01-15 Added screw terminal headers
2019-01-15 Placed another screw terminal
2019-01-15 More screw terminals
2019-01-16 Fixed silkscreen
2019-01-16 Added mounting holes, logo
2019-01-16 fixed air wires
2019-01-17 fixes
2019-01-17 Added HV warning. Moved current sense to after switch
2019-01-17 Fixed all errors
2019-01-17 current sense routing fix and high voltage keepout
2019-01-17 flyback diode fix
2019-01-18 added fuse amperage in silkscreen
2019-01-20 increased blender vias to gnd, added individual blender fuses,addition aref cap, and debug leds
2019-01-20 mapped additional elevator encoder input
2019-01-20 Moved uc pins; fixed all DRCs
2019-01-21 broke blender enable to terminal blocks
2019-01-22 Morning changes from board review
2019-01-22 Finished review changes
2019-01-22 Few more changes
2019-01-22 Renumbered components
2019-01-22 Added labels to connectors
2019-01-23 added gnd vias for mains
2019-01-23 added gnd planes for high current parts
2019-01-27 Updated pdf of schematic
2019-02-14 Started wiring diagram
2019-02-15 Added fuses and switch

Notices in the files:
parts and their libraries:
SparkFun-Capacitors: Licensing: Creative Commons ShareAlike 4.0 International - https://creativecommons.org/licenses/by-sa/4.0
